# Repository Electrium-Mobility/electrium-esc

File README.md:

# electrium-esc
The repository for the custom ESC (motor controller) built by Electrium Mobility, a design team at the University of Waterloo. The ESC is used to power portable electric vehicles. There are multiple branches which specify which electric vehicle the device is used for

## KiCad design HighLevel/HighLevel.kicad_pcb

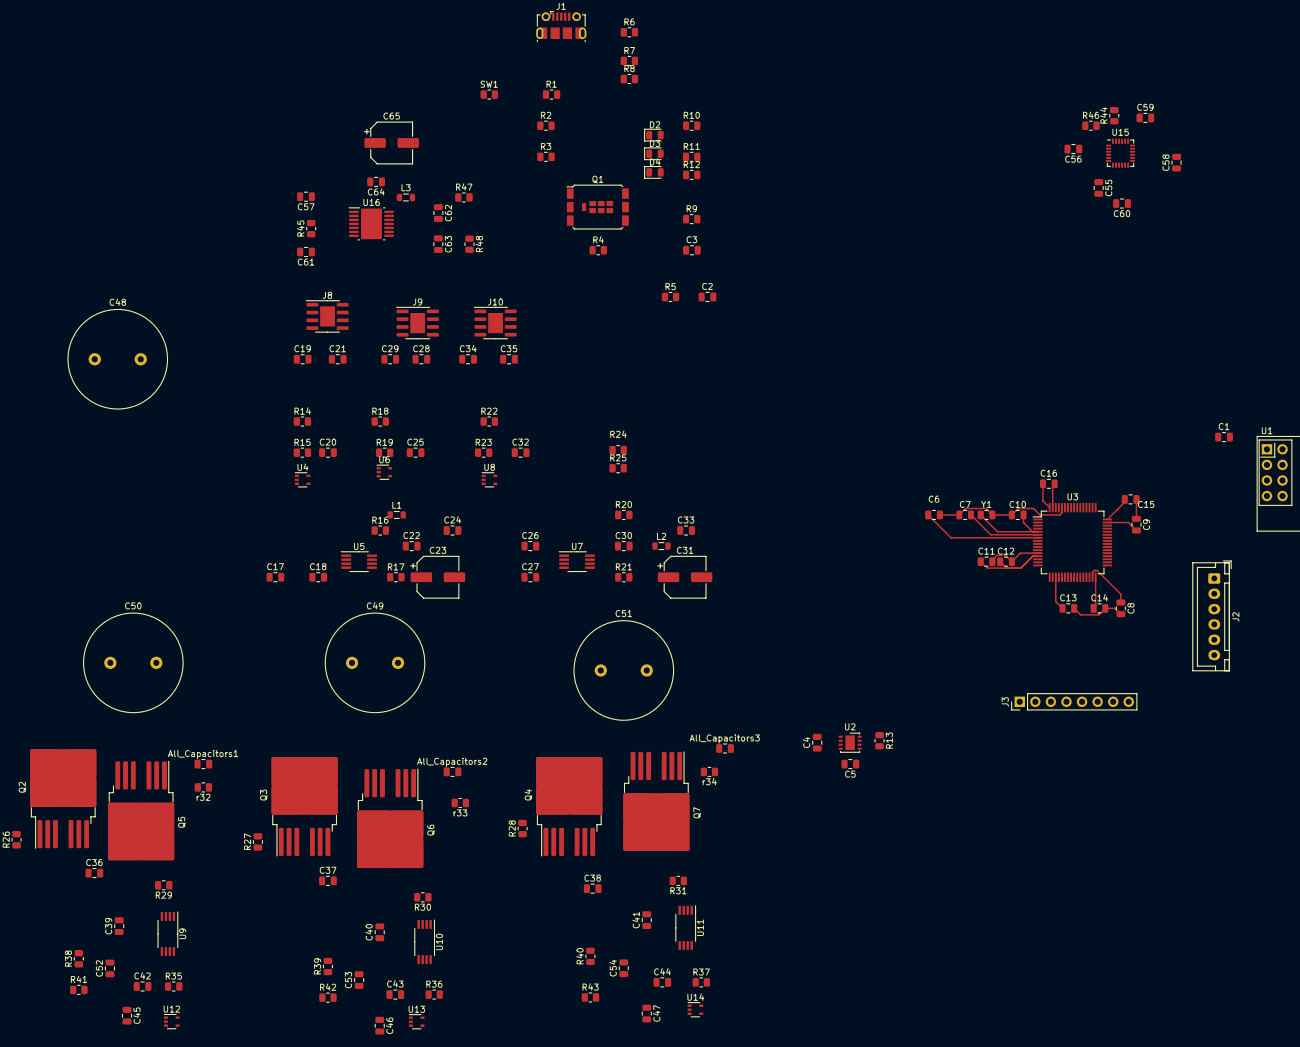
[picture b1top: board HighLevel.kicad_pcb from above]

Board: 2 copper layers, 153 parts (0 on the bottom side), 106 nets.

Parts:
All_Capacitors1, All_Capacitors2, All_Capacitors3: 4.7u_100V; C_0805_2012Metric
C1, C4, C5, C8, C9, C11, C12, C13, C14, C15, C16, C17, C18, C19, C24, C26, C27, C28, C33, C34, C39, C40, C41, C52, C53, C54, C55, C56, C58, C60, C63, C64: 2.2u; C_0805_2012Metric
C2, C3, C6, C20, C21, C22, C25, C29, C30, C32, C35, C59, C62: 100n; C_0805_2012Metric
C7, C10: 15p; C_0805_2012Metric
C23, C31: 100u; CP_Elec_6.3x7.7
C36, C37, C38: C; C_0805_2012Metric
C42, C43, C44: 15n; C_0805_2012Metric
C45, C46, C47: 1n; C_0805_2012Metric
C48, C49, C50, C51: 470u_80V; C_Radial_D16.0mm_H31.5mm_P7.50mm
C57: 4.7u_100V; C_0805_2012Metric
C61: 10n; C_0805_2012Metric
C65: 22u_16V; CP_Elec_6.3x7.7
D2: BLUE; LED_0805_2012Metric
D3: RED; LED_0805_2012Metric
D4: GREEN; LED_0805_2012Metric
J1: USB_A; USB_Micro-B_Molex-105017-0001
J2: Conn_01x06; JST_XH_B6B-XH-A_1x06_P2.50mm_Vertical
J3: COMM; PinHeader_1x08_P2.54mm_Vertical
J8, J9, J10: UCC27210DDA; SOIC-8-1EP_3.9x4.9mm_P1.27mm_EP2.41x3.3mm
L1, L2: 22u; L_0805_2012Metric
L3: 100u; L_0805_2012Metric
Q1: MOFSET_N; DirectFET_L6
Q2, Q3, Q4, Q5, Q6, Q7: IPB039N10N3G; TO-263-6
R1, R2, R3, R4: 2k2; R_0805_2012Metric
R5: 100R; R_0805_2012Metric
R6: 0R; R_0805_2012Metric
R7, R8, R11, R12, R13: 220R; R_0805_2012Metric
R9, R17, R21, R41, R42, R43, R47: 10k; R_0805_2012Metric
R10, R35, R36, R37, R44, R46: 1k; R_0805_2012Metric
R14, R18, R22, R24: 56k; R_0805_2012Metric
R15, R19, R23, R25: 2.2k; R_0805_2012Metric
R16, R20: 52.3k; R_0805_2012Metric
R26, R27, R28: 1R; R_0805_2012Metric
R29, R30, R31: 0.005; R_0805_2012Metric
R38, R39, R40: NTC 10k; R_0805_2012Metric
R45: 402k; R_0805_2012Metric
R48: 2k; R_0805_2012Metric
SW1: SW_SPDT; R_0805_2012Metric
U1: NRF24L01_Breakout; nRF24L01_Breakout
U2: TJA1051TK-3; DFN-8-1EP_3x3mm_P0.65mm_EP1.55x2.4mm
U3: STM32F405RGTx; LQFP-64_10x10mm_P0.5mm
U4, U6, U8, U12, U13, U14: MC74VHC1GT66; SOT-353_SC-70-5
U5, U7: MCP16311MS; MSOP-8_3x3mm_P0.65mm
U9, U10, U11: INA240A4PW; TSSOP-8_4.4x3mm_P0.65mm
U15: MPU-9150; InvenSense_QFN-24_4x4mm_P0.5mm
U16: LM5161PWP; HTSSOP-14-1EP_4.4x5mm_P0.65mm_EP3.4x5mm_Mask3x3.1mm
Y1: C_0805_2012Metric
r32, r33, r34: 1R; R_0805_2012Metric

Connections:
+5V: C4.1, J3.1, R6.1, R16.2, R20.2, U2.3 (VCC)
+12V: C17.1, C19.1, C26.1, C28.1, C34.1, C64.1, C65.1, J8.1 (VDD), J9.1 (VDD), J10.1 (VDD), L3.1, R47.1, U5.3 (EN), U5.4 (Vin), U7.3 (EN), U7.4 (Vin)
/CAN/CANH: R13.1, U2.7 (CANH)
/CAN/CANL: R13.2, U2.6 (CANL)
/CAN/RXD: U2.4 (RXD), U3.61 (PB8)
/CAN/TXD: U2.1 (TXD), U3.62 (PB9)
/IMU/SCL: J3.6, R46.2, U3.23 (PA7), U15.23 (SCL)
/IMU/SDA: J3.5, R44.2, U3.20 (PA4), U3.30 (PB11), U15.24 (SDA)
/MCU/ADC_15: J3.8, U3.25 (PC5)
/MCU/ADC_TEMP: C52.1, R38.1, R41.2, U3.17 (PA3)
/MCU/ADC_TEMP2: C53.1, R39.1, R42.2, U3.26 (PB0)
/MCU/ADC_TEMP3: C54.1, R40.1, R43.2, U3.27 (PB1)
/MCU/AN_IN: R24.1, R25.1, U3.11 (PC3)
/MCU/CURRENT_1: C45.1, R35.1, U3.8 (PC0), U12.1 (IN/OUT_XA)
/MCU/CURRENT_2: C46.1, R36.1, U3.9 (PC1), U13.1 (IN/OUT_XA)
/MCU/CURRENT_3: C47.1, R37.1, U3.10 (PC2), U14.1 (IN/OUT_XA)
/MCU/CURR_FILTER: U3.54 (PD2), U12.4 (ON/OFF_CONTROL), U13.4 (ON/OFF_CONTROL), U14.4 (ON/OFF_CONTROL)
/MCU/H1: J8.5 (HI), U3.41 (PA8)
/MCU/H2: J9.5 (HI), U3.42 (PA9)
/MCU/H3: J10.5 (HI), U3.43 (PA10)
/MCU/HALL_1: J2.5, R3.1, U3.37 (PC6)
/MCU/HALL_2: J2.4, R2.1, U3.38 (PC7)
/MCU/HALL_3: J2.3, R1.1, U3.39 (PC8)
/MCU/L1: J8.6 (LI), U3.34 (PB13)
/MCU/L2: J9.6 (LI), U3.35 (PB14)
/MCU/L3: J10.6 (LI), U3.36 (PB15)
/MCU/LED_GREEN: D4.2 (A), U3.57 (PB5)
/MCU/LED_RED: D3.2 (A), U3.59 (PB7)
/MCU/MISO_ADC_EXT2: J3.7, U3.22 (PA6)
/MCU/NRST: C6.1, U3.7 (NRST)
/MCU/PC9: U3.40 (PC9), U4.4 (ON_OFF), U6.4 (ON_OFF), U8.4 (ON_OFF)
/MCU/PC13: Q1.2 (G), R4.1, U3.2 (PC13)
/MCU/SCK_ADC_EXT: J3.4, U3.21 (PA5)
/MCU/SERVO: C2.1, R5.1, U3.58 (PB6)
/MCU/SPI3_CE: U1.3 (CE), U3.3 (PC14)
/MCU/SPI3_CSN: U1.4 (~CSN), U3.4 (PC15)
/MCU/SPI3_MISO: U1.7 (MISO), U3.52 (PC11)
/MCU/SPI3_MOSI: U1.6 (MOSI), U3.53 (PC12)
/MCU/SPI3_SCK: U1.5 (SCK), U3.51 (PC10)
/MCU/TEMP_MOTOR: C3.1, J2.2, R9.2, U3.24 (PC4)
/MCU/USB_DM: R8.1, U3.44 (PA11)
/MCU/USB_DP: R7.1, U3.45 (PA12)
/MCU/Voltage_1: C20.1, R14.1, R15.1, U3.14 (PA0)
/MCU/Voltage_2: C25.1, R18.1, R19.1, U3.15 (PA1)
/MCU/Voltage_3: C32.1, R22.1, R23.1, U3.16 (PA2)
/driver/HO1: J8.3 (HO), R26.2
/driver/HO2: J9.3 (HO), R27.2
/driver/HO3: J10.3 (HO), R28.2
/driver/HS1: C21.2, J8.4 (HS), Q2.2 (S), Q2.3 (S), Q2.5 (S), Q2.6 (S), Q2.7 (S), Q5.4 (D), R14.2, R29.1, U9.2 (+)
/driver/HS2: C29.2, J9.4 (HS), Q3.2 (S), Q3.3 (S), Q3.5 (S), Q3.6 (S), Q3.7 (S), Q6.4 (D), R18.2, R22.2, R30.1, U10.2 (+)
/driver/HS3: C35.2, J10.4 (HS), Q4.2 (S), Q4.3 (S), Q4.5 (S), Q4.6 (S), Q4.7 (S), Q7.4 (D), R31.1, U11.2 (+)
/driver/LO1: J8.8 (LO), r32.1
/driver/LO2: J9.8 (LO), r33.1
/driver/LO3: J10.8 (LO), r34.1
/power/C_A: R35.2, U9.8
/power/C_B: R36.2, U10.8
/power/C_C: R37.2, U11.8
GND: All_Capacitors1.2, All_Capacitors2.2, All_Capacitors3.2, C1.1, C2.2, C3.2, C4.2, C5.2, C6.2, C7.1, C8.2, C9.1, C10.1, C11.2, C12.2, C13.2, C14.2, C15.2, C16.2, C17.2, C18.2, C19.2, C23.2, C24.1, C26.2, C27.2, C28.2, C31.2, C33.1, C34.2, C36.2, C37.2, C38.2, C39.2, C40.2, C41.2, C42.1, C43.1, C44.1, C45.2, C46.2, C47.2, C48.2, C49.2, C50.2, C51.2, C52.2, C53.2, C54.2, C55.2, C56.2, C57.2, C58.2, C59.2, C60.2, C61.2, C63.2, C64.2, C65.2, J1.4 (GND), J1.5 (Shield), J2.6, J3.3, J8.7 (VSS), J8.9 (EP), J9.7 (VSS), J9.9 (EP), J10.7 (VSS), J10.9 (EP), Q1.1 (D), Q5.2 (S), Q5.3 (S), Q5.5 (S), Q5.6 (S), Q5.7 (S), Q6.2 (S), Q6.3 (S), Q6.5 (S), Q6.6 (S), Q6.7 (S), Q7.2 (S), Q7.3 (S), Q7.5 (S), Q7.6 (S), Q7.7 (S), R4.2, R10.1, R11.1, R12.1, R15.2, R17.1, R19.2, R21.1, R23.2, R25.2, R41.1, R42.1, R43.1, R48.2, U1.1 (GND), U2.2 (GND), U2.8 (S), U2.9 (GND), U3.12 (VSSA), U3.18 (VSS), U3.60 (BOOT0), U3.63 (VSS), U4.2 (OI_YA), U4.3 (GND), U5.5 (PGND), U5.8 (AGND), U6.2 (OI_YA), U6.3 (GND), U7.5 (PGND), U7.8 (AGND), U8.2 (OI_YA), U8.3 (GND), U9.1 (GND), U9.4 (GND), U9.7 (REF1), U10.1 (GND), U10.4 (GND), U10.7 (REF1), U11.1 (GND), U11.4 (GND), U11.7 (REF1), U12.3 (GND), U13.3 (GND), U14.3 (GND), U15.9 (AD0), U15.15 (GND), U15.17 (GND), U15.18 (GND), U16.1 (AGND), U16.2 (PGND), U16.8 (FPWM), U16.15 (AGND), Y1.2
unnamed: C62.1, L3.2, U16.12 (SW), U16.13 (SW)
unnamed: D2.1 (K), R10.2
unnamed: D3.1 (K), R11.2
unnamed: D4.1 (K), R12.2
unnamed: J1.3 (D+), R7.2
unnamed: J1.2 (D-), R8.2
unnamed: J1.1 (VBUS), R6.2
unnamed: J2.1, R1.2, R2.2, R3.2, SW1.2 (B)
unnamed: C21.1, J8.2 (HB)
unnamed: C29.1, J9.2 (HB)
unnamed: C35.1, J10.2 (HB)
unnamed: All_Capacitors1.1, C36.1, Q2.1 (G), R26.1
unnamed: All_Capacitors2.1, C37.1, Q3.1 (G), R27.1
unnamed: All_Capacitors3.1, C38.1, Q4.1 (G), R28.1
unnamed: Q5.1 (G), r32.2
unnamed: Q6.1 (G), r33.2
unnamed: Q7.1 (G), r34.2
unnamed: C5.1, U2.5 (VIO)
unnamed: C10.2, U3.5 (PH0), Y1.1
unnamed: C7.2, U3.6 (PH1)
unnamed: C8.1, U3.31 (VCAP_1)
unnamed: C9.2, U3.47 (VCAP_2)
unnamed: C20.2, U4.1 (IO_XA)
unnamed: C22.2, U5.7 (BOOST)
unnamed: C22.1, L1.1, U5.6 (SW)
unnamed: C18.1, U5.2 (Vcc)
unnamed: C23.1, C24.2, L1.2, R16.1, R17.2, U5.1 (Vfb)
unnamed: C25.2, U6.1 (IO_XA)
unnamed: C30.2, U7.7 (BOOST)
unnamed: C30.1, L2.1, U7.6 (SW)
unnamed: C27.1, U7.2 (Vcc)
unnamed: C31.1, C33.2, L2.2, R20.1, R21.2, U7.1 (Vfb)
unnamed: C32.2, U8.1 (IO_XA)
unnamed: R29.2, U9.3 (-)
unnamed: R30.2, U10.3 (-)
unnamed: R31.2, U11.3 (-)
unnamed: C42.2, U12.2 (OUT/IN_YA)
unnamed: C43.2, U13.2 (OUT/IN_YA)
unnamed: C44.2, U14.2 (OUT/IN_YA)
unnamed: C59.1, U15.20 (CPOUT)
unnamed: C60.1, U15.10 (REGOUT)
unnamed: C62.2, U16.11 (BST)
unnamed: R47.2, R48.1, U16.9 (FB)
unnamed: R45.1, U16.5 (RON)
unnamed: C61.1, U16.6 (SS)
unnamed: C63.1, U16.10 (VCC)
VCC: C1.2, C11.1, C12.1, C13.1, C14.1, C15.1, C16.1, C39.1, C40.1, C41.1, C55.1, C56.1, C58.1, D2.2 (A), J3.2, R9.1, R38.2, R39.2, R40.2, R44.1, R46.1, SW1.1 (A), U1.2 (VCC), U3.1 (VBAT), U3.13 (VDDA), U3.19 (VDD), U3.32 (VDD), U3.48 (VDD), U3.64 (VDD), U4.5 (VCC), U6.5 (VCC), U8.5 (VCC), U9.5 (V+), U9.6 (REF2), U10.5 (V+), U10.6 (REF2), U11.5 (V+), U11.6 (REF2), U12.5 (VCC), U13.5 (VCC), U14.5 (VCC), U15.3 (VDD), U15.8 (VLOGIC), U15.13 (VDD)
V_IN: C48.1, C49.1, C50.1, C51.1, C57.1, Q2.4 (D), Q3.4 (D), Q4.4 (D), R24.2, R45.2, U16.3 (VIN), U16.4 (EN/UVLO)

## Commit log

2023-05-21 High-level block diagram
2023-05-21 Add current sense and finish DRV8301 Circuit
2023-05-21 Complete transistor stage
2023-05-21 Finish current sense
2023-05-21 Finish up current sense
2023-05-23 Most updated changes
2023-05-24 high level project file added
2023-05-28 Create MCU.kicad_sch
    Created sheet for MCU
2023-05-28 Create CAN schematic
2023-05-28 Finish MCU
    Updated MCU as per drawing
2023-05-30 Minor fixes
    Fixed some wires that were not connected to capacitor
2023-05-31 Create driver schematic
2023-06-02 added current sensing circuit in power.kicad_sch
2023-06-02 move power.sch into high level directory
2023-06-04 add: updated power file
2023-06-10 Added Buck Converter
    Added Buck Converter schematic
2023-06-10 Update MCU.kicad_sch
    Changed MCU name
2023-06-12 small changes to some auxiliary files
2023-06-18 update: include footprints, remove previous power files
    Fix Power file with updates, footprints included.
2023-06-18 highlevel update
2023-06-18 high level stuff
2023-06-19 added footprints and changed to hierarchical labels
2023-06-24 change labels from global to hierarchical in power_v2.sch
2023-06-26 Final High Level + edits + footprint
2023-06-26 fix: update labels and fix conflicts for power file
2023-06-29 Fix all errors
2023-06-29 Update power schematic to use TO-263 transistor
2023-06-30 Started PCB and added connections to MCU
2023-07-01 Added last two sheets and some footprints
2023-07-21 Arranged components on PCB
2023-07-22 Updated Driver on PCB
